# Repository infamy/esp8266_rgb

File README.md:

# ESP8266 RGB NeoPixel Control Board

Uses a level shifter to get reliable communication with the NeoPixel. Has a 5v Regulator to drop the 12v input to 5v to allow it to run on the same powersupply as the LED.

Current software implements ArtNet (DMX512) over Wifi.

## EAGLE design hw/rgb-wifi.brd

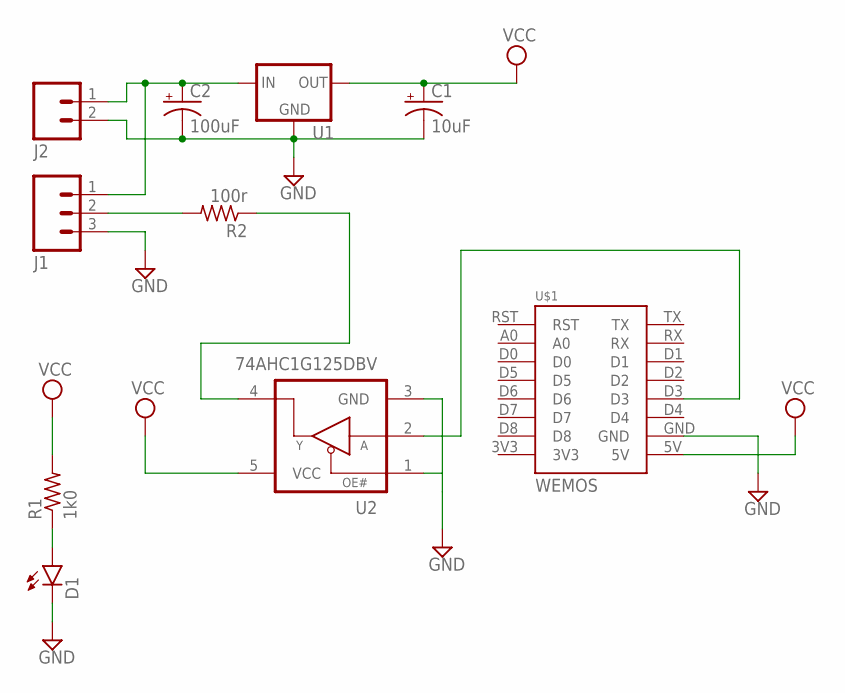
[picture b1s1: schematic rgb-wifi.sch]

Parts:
C1: 10uF; CPOL-RADIAL-10UF-25V
C2: 100uF; CPOL-RADIAL-100UF-25V
D1: LED3MM
J1: M03SCREW; SCREWTERMINAL-3.5MM-3
J2: M023.5MM; SCREWTERMINAL-3.5MM-2
R1: 1k0; 0204V
R2: 100r; 0204V
U1: +12v; TO-252
U2: 74AHC1G125DBV; SOT23-5
U$1: WEMOS

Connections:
GND: C1.2 (-), C2.2 (-), D1.K (C), J1.3, J2.2, U1.3 (GND), U2.1 (OE#), U2.3 (GND), U$1.GND
unnamed: C2.1 (+), J1.1, J2.1, U1.1 (IN)
unnamed: D1.A, R1.1
unnamed: J1.2, R2.2
unnamed: R2.1, U2.4 (Y)
unnamed: U2.2 (A), U$1.D3
VCC: C1.1 (+), R1.2, U1.2 (OUT), U2.5 (VCC), U$1.5V

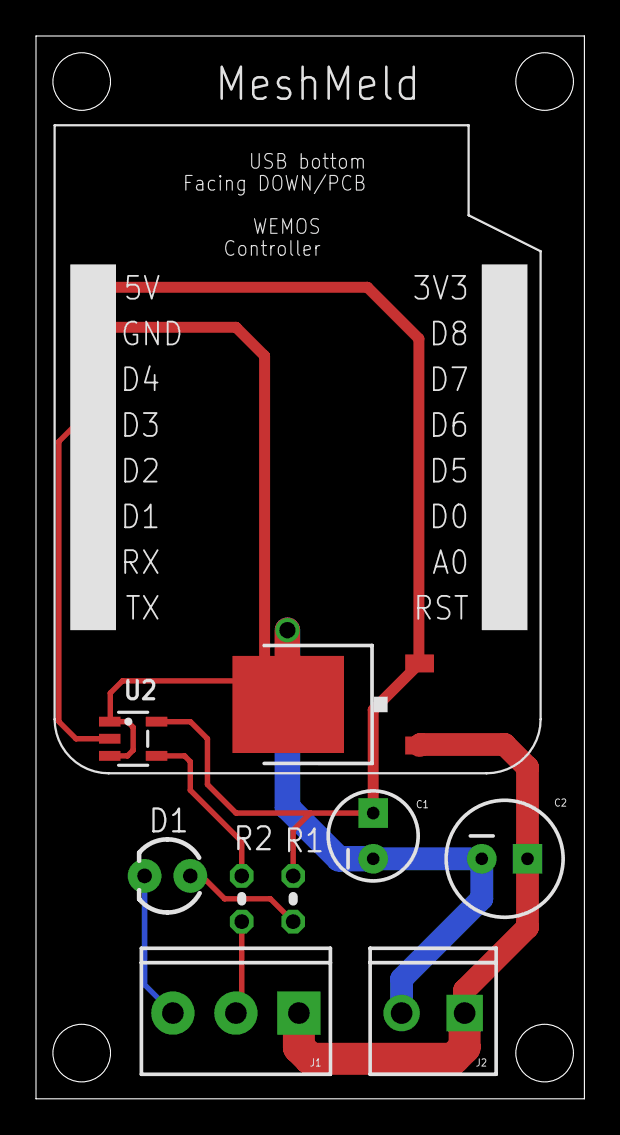
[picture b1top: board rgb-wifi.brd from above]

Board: 2 copper layers, 30.5 x 59.0 mm, 10 parts (0 on the bottom side), 7 nets.

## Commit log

2017-08-12 Initial checking
2017-08-12 added board images
2017-08-12 add source code

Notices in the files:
parts and their libraries:
SparkFun-Capacitors: Licensing: Creative Commons ShareAlike 4.0 International - https://creativecommons.org/licenses/by-sa/4.0
74ah: Copyright (C) 2007, Bob Starr
